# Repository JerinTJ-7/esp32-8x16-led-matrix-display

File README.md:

# ESP32 8×16 LED Matrix Display Board

## Overview

This project is a custom PCB-based LED matrix display designed using KiCad.

The system uses:
- ESP32 DevKit V1
- 74HC595 Shift Registers
- LED Matrix (8×16)
- Blynk IoT
- Wokwi Simulation

## Features

- Text display
- Scrolling messages
- Wi-Fi connectivity
- Mobile control using Blynk
- Custom KiCad PCB

## Tools Used

- KiCad 9
- Arduino IDE
- Wokwi Simulator
- Blynk IoT

## Images

## Files

- KiCad Design Files
- Gerbers
- BOM
- Arduino Firmware
- Project Report

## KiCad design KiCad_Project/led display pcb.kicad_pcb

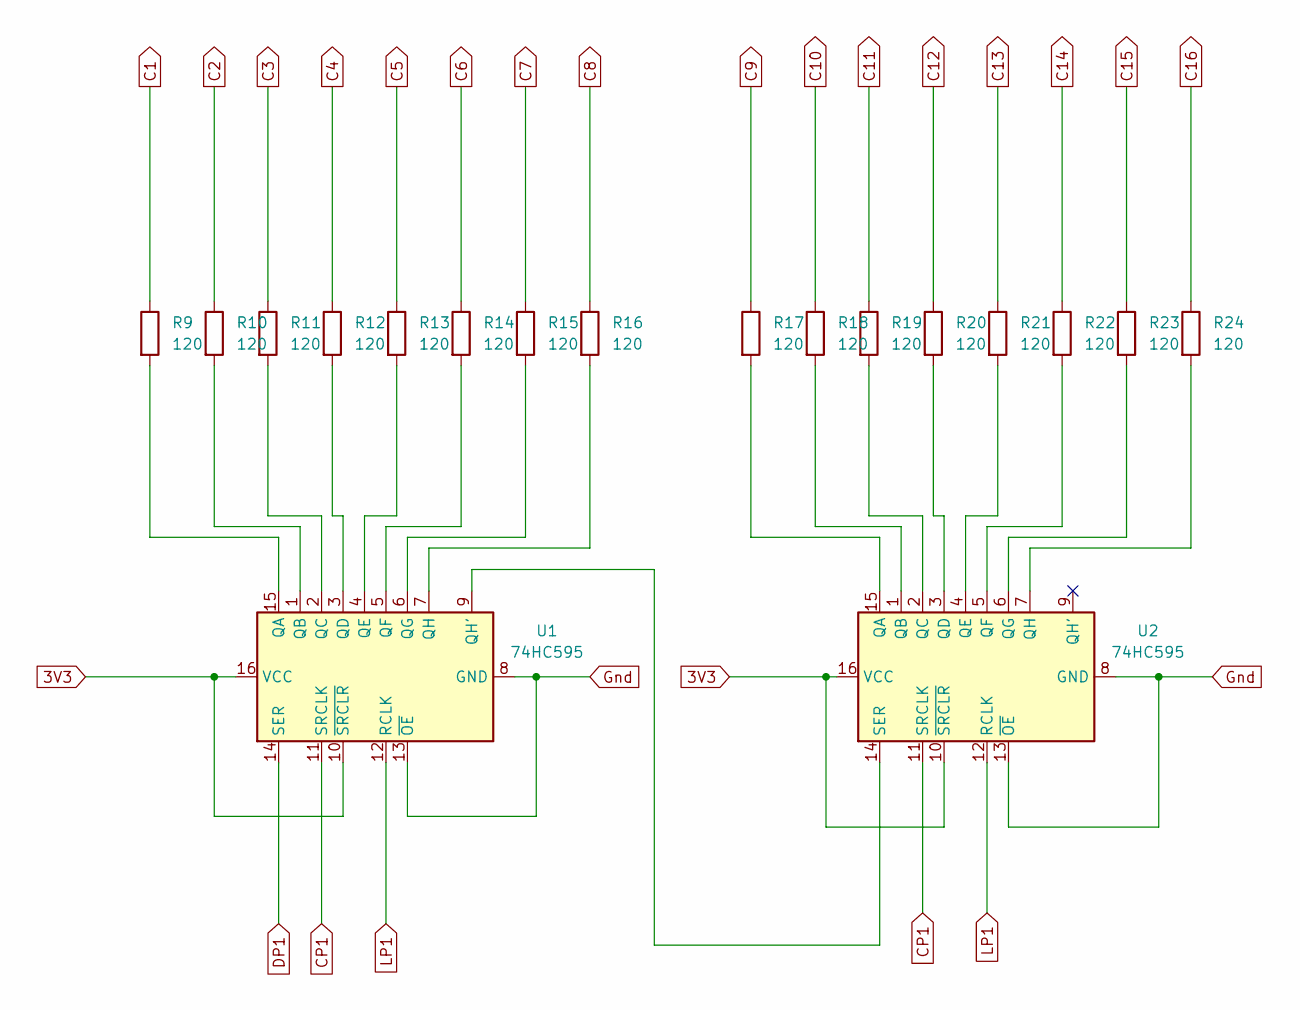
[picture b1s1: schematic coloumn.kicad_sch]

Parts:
R9, R10, R11, R12, R13, R14, R15, R16, R17, R18, R19, R20, R21, R22, R23, R24: 120; R_Axial_DIN0204_L3.6mm_D1.6mm_P5.08mm_Horizontal
U1, U2: 74HC595; DIP-16_W7.62mm

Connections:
3V3: U1.10 (~SRCLR), U1.16 (VCC), U2.10 (~SRCLR), U2.16 (VCC); also elsewhere on the board
C1: R9.1; also elsewhere on the board
C2: R10.1; also elsewhere on the board
C3: R11.1; also elsewhere on the board
C4: R12.1; also elsewhere on the board
C5: R13.1; also elsewhere on the board
C6: R14.1; also elsewhere on the board
C7: R15.1; also elsewhere on the board
C8: R16.1; also elsewhere on the board
C9: R17.1; also elsewhere on the board
C10: R18.1; also elsewhere on the board
C11: R19.1; also elsewhere on the board
C12: R20.1; also elsewhere on the board
C13: R21.1; also elsewhere on the board
C14: R22.1; also elsewhere on the board
C15: R23.1; also elsewhere on the board
C16: R24.1; also elsewhere on the board
CP1: U1.11 (SRCLK), U2.11 (SRCLK); also elsewhere on the board
DP1: U1.14 (SER); also elsewhere on the board
Gnd: U1.8 (GND), U1.13 (~OE), U2.8 (GND), U2.13 (~OE); also elsewhere on the board
LP1: U1.12 (RCLK), U2.12 (RCLK); also elsewhere on the board
unnamed: R9.2, U1.15 (QA)
unnamed: R10.2, U1.1 (QB)
unnamed: R11.2, U1.2 (QC)
unnamed: R12.2, U1.3 (QD)
unnamed: R13.2, U1.4 (QE)
unnamed: R14.2, U1.5 (QF)
unnamed: R15.2, U1.6 (QG)
unnamed: U1.9 (QH'), U2.14 (SER)
unnamed: R16.2, U1.7 (QH)
unnamed: R17.2, U2.15 (QA)
unnamed: R18.2, U2.1 (QB)
unnamed: R19.2, U2.2 (QC)
unnamed: R20.2, U2.3 (QD)
unnamed: R21.2, U2.4 (QE)
unnamed: R22.2, U2.5 (QF)
unnamed: R23.2, U2.6 (QG)
unnamed: R24.2, U2.7 (QH)

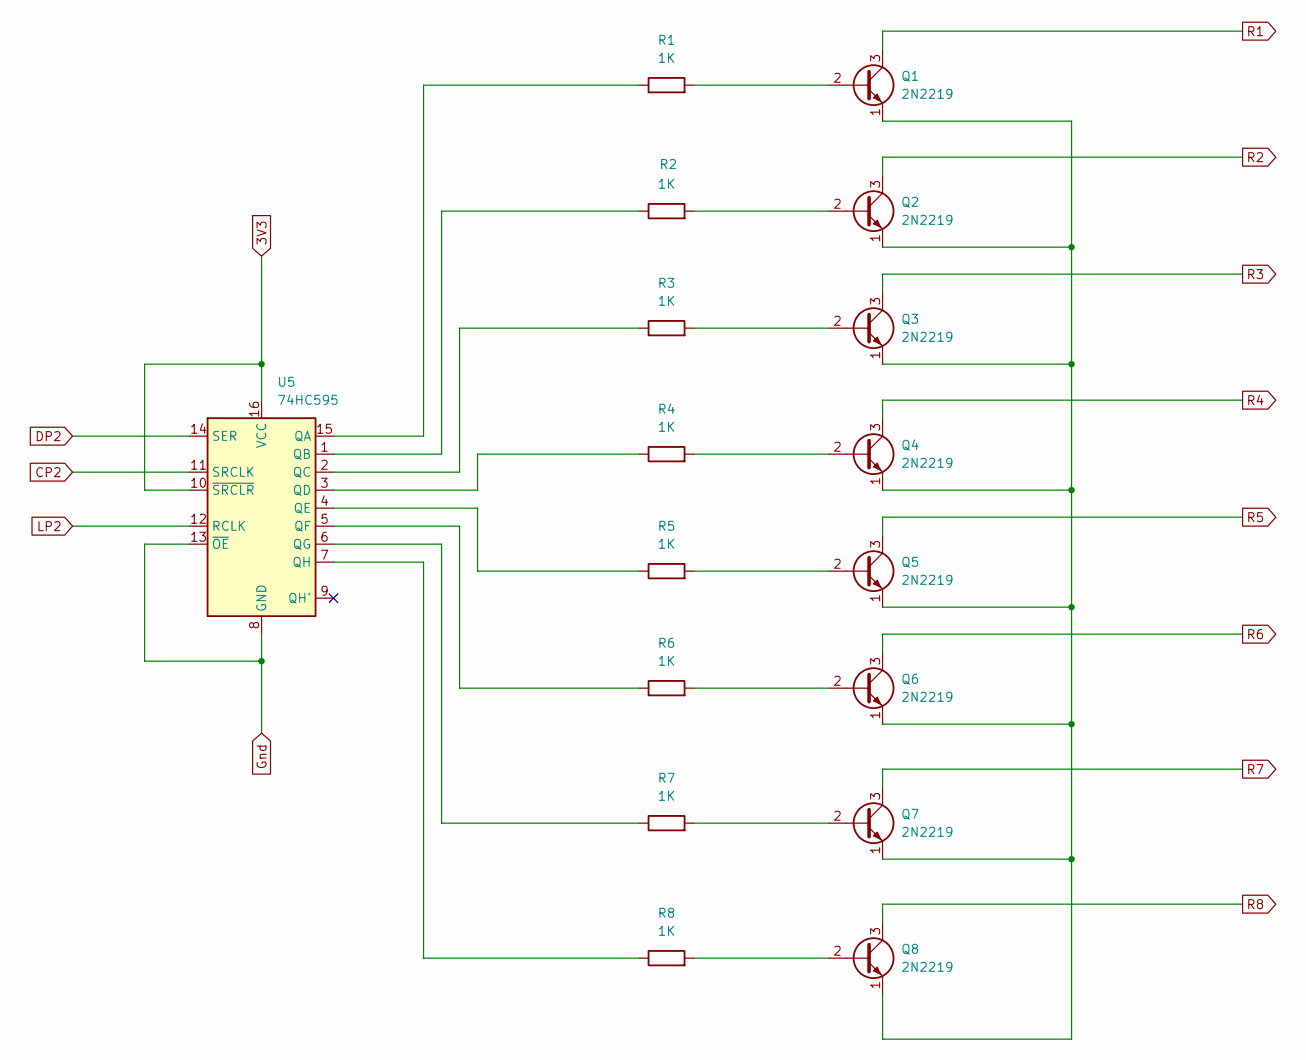
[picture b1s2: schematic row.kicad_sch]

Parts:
Q1, Q2, Q3, Q4, Q5, Q6, Q7, Q8: 2N2219; TO-39-3
R1, R2, R3, R4, R5, R6, R7, R8: 1K; R_Axial_DIN0204_L3.6mm_D1.6mm_P5.08mm_Horizontal
U5: 74HC595; DIP-16_W7.62mm

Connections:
3V3: U5.10 (~SRCLR), U5.16 (VCC); also elsewhere on the board
CP2: U5.11 (SRCLK); also elsewhere on the board
DP2: U5.14 (SER); also elsewhere on the board
Gnd: U5.8 (GND), U5.13 (~OE); also elsewhere on the board
LP2: U5.12 (RCLK); also elsewhere on the board
unnamed: Q1.2 (B), R1.2
unnamed: Q1.1 (E), Q2.1 (E), Q3.1 (E), Q4.1 (E), Q5.1 (E), Q6.1 (E), Q7.1 (E), Q8.1 (E)
unnamed: Q2.2 (B), R2.2
unnamed: Q3.2 (B), R3.2
unnamed: Q4.2 (B), R4.2
unnamed: Q5.2 (B), R5.2
unnamed: Q6.2 (B), R6.2
unnamed: Q7.2 (B), R7.2
unnamed: Q8.2 (B), R8.2
unnamed: R1.1, U5.15 (QA)
unnamed: R2.1, U5.1 (QB)
unnamed: R3.1, U5.2 (QC)
unnamed: R4.1, U5.3 (QD)
unnamed: R5.1, U5.4 (QE)
unnamed: R6.1, U5.5 (QF)
unnamed: R7.1, U5.6 (QG)
unnamed: R8.1, U5.7 (QH)
R1: Q1.3 (C); also elsewhere on the board
R2: Q2.3 (C); also elsewhere on the board
R3: Q3.3 (C); also elsewhere on the board
R4: Q4.3 (C); also elsewhere on the board
R5: Q5.3 (C); also elsewhere on the board
R6: Q6.3 (C); also elsewhere on the board
R7: Q7.3 (C); also elsewhere on the board
R8: Q8.3 (C); also elsewhere on the board

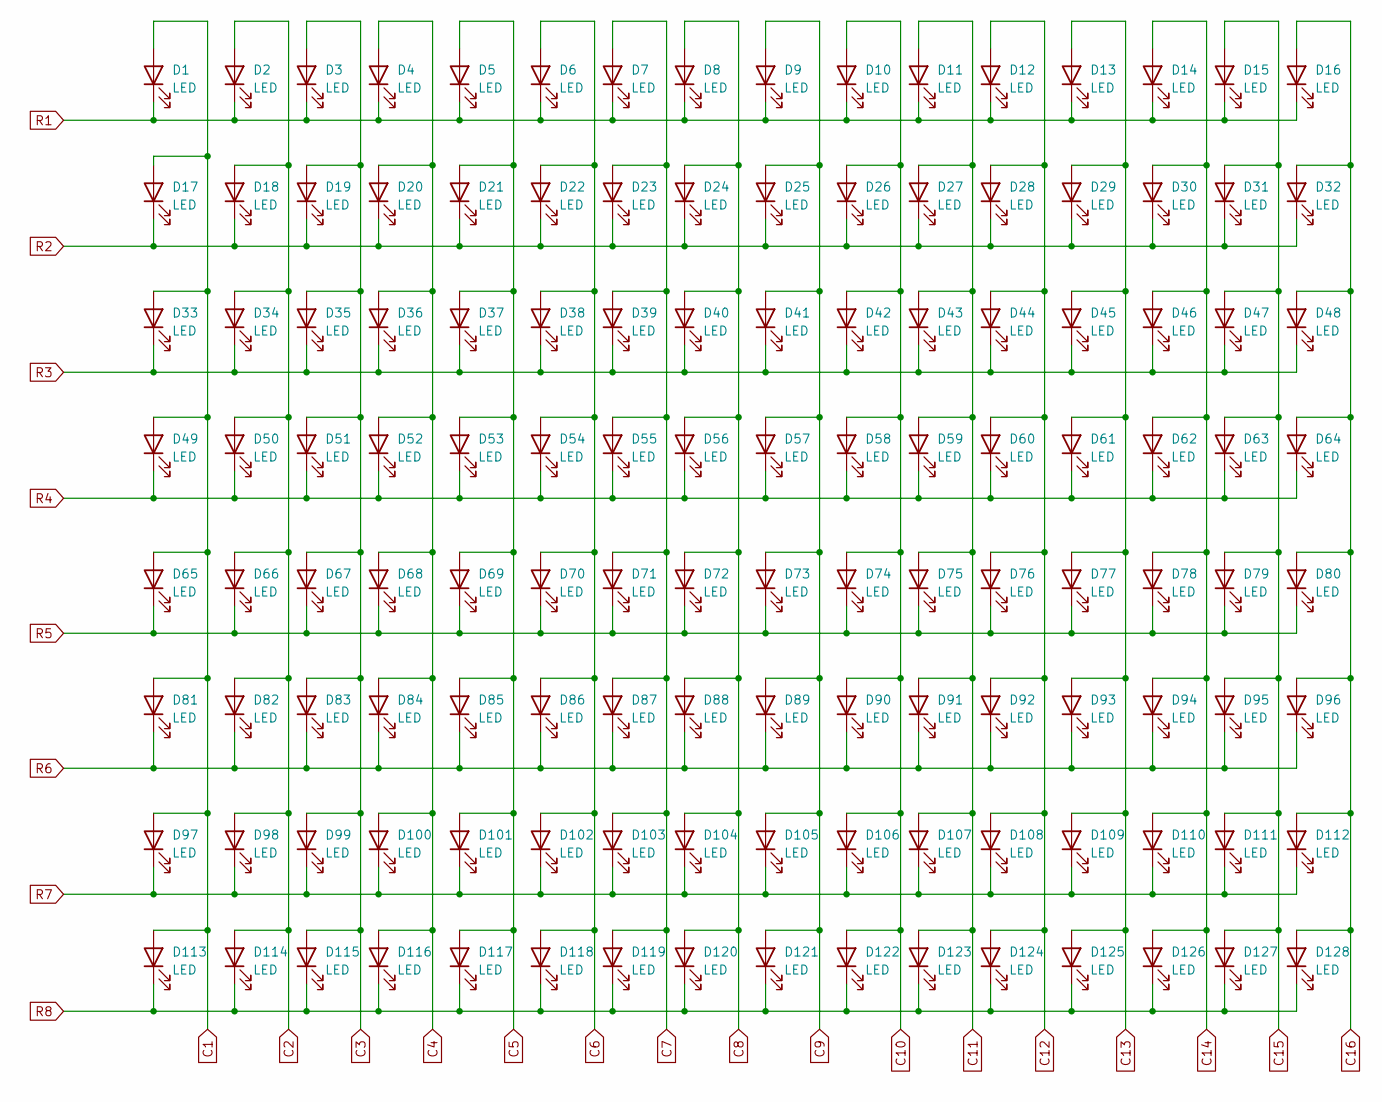
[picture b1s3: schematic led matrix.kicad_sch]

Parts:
D1, D2, D3, D4, D5, D6, D7, D8, D9, D10, D11, D12, D13, D14, D15, D16, D17, D18, D19, D20, D21, D22, D23, D24, D25, D26, D27, D28, D29, D30, D31, D32, D33, D34, D35, D36, D37, D38, D39, D40, D41, D42, D43, D44, D45, D46, D47, D48, D49, D50, D51, D52, D53, D54, D55, D56, D57, D58, D59, D60, D61, D62, D63, D64, D65, D66, D67, D68, D69, D70, D71, D72, D73, D74, D75, D76, D77, D78, D79, D80, D81, D82, D83, D84, D85, D86, D87, D88, D89, D90, D91, D92, D93, D94, D95, D96, D97, D98, D99, D100, D101, D102, D103, D104, D105, D106, D107, D108, D109, D110, D111, D112, D113, D114, D115, D116, D117, D118, D119, D120, D121, D122, D123, D124, D125, D126, D127, D128: LED; LED_D5.0mm

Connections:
C1: D1.2 (A), D17.2 (A), D33.2 (A), D49.2 (A), D65.2 (A), D81.2 (A), D97.2 (A), D113.2 (A); also elsewhere on the board
C2: D2.2 (A), D18.2 (A), D34.2 (A), D50.2 (A), D66.2 (A), D82.2 (A), D98.2 (A), D114.2 (A); also elsewhere on the board
C3: D3.2 (A), D19.2 (A), D35.2 (A), D51.2 (A), D67.2 (A), D83.2 (A), D99.2 (A), D115.2 (A); also elsewhere on the board
C4: D4.2 (A), D20.2 (A), D36.2 (A), D52.2 (A), D68.2 (A), D84.2 (A), D100.2 (A), D116.2 (A); also elsewhere on the board
C5: D5.2 (A), D21.2 (A), D37.2 (A), D53.2 (A), D69.2 (A), D85.2 (A), D101.2 (A), D117.2 (A); also elsewhere on the board
C6: D6.2 (A), D22.2 (A), D38.2 (A), D54.2 (A), D70.2 (A), D86.2 (A), D102.2 (A), D118.2 (A); also elsewhere on the board
C7: D7.2 (A), D23.2 (A), D39.2 (A), D55.2 (A), D71.2 (A), D87.2 (A), D103.2 (A), D119.2 (A); also elsewhere on the board
C8: D8.2 (A), D24.2 (A), D40.2 (A), D56.2 (A), D72.2 (A), D88.2 (A), D104.2 (A), D120.2 (A); also elsewhere on the board
C9: D9.2 (A), D25.2 (A), D41.2 (A), D57.2 (A), D73.2 (A), D89.2 (A), D105.2 (A), D121.2 (A); also elsewhere on the board
C10: D10.2 (A), D26.2 (A), D42.2 (A), D58.2 (A), D74.2 (A), D90.2 (A), D106.2 (A), D122.2 (A); also elsewhere on the board
C11: D11.2 (A), D27.2 (A), D43.2 (A), D59.2 (A), D75.2 (A), D91.2 (A), D107.2 (A), D123.2 (A); also elsewhere on the board
C12: D12.2 (A), D28.2 (A), D44.2 (A), D60.2 (A), D76.2 (A), D92.2 (A), D108.2 (A), D124.2 (A); also elsewhere on the board
C13: D13.2 (A), D29.2 (A), D45.2 (A), D61.2 (A), D77.2 (A), D93.2 (A), D109.2 (A), D125.2 (A); also elsewhere on the board
C14: D14.2 (A), D30.2 (A), D46.2 (A), D62.2 (A), D78.2 (A), D94.2 (A), D110.2 (A), D126.2 (A); also elsewhere on the board
C15: D15.2 (A), D31.2 (A), D47.2 (A), D63.2 (A), D79.2 (A), D95.2 (A), D111.2 (A), D127.2 (A); also elsewhere on the board
C16: D16.2 (A), D32.2 (A), D48.2 (A), D64.2 (A), D80.2 (A), D96.2 (A), D112.2 (A), D128.2 (A); also elsewhere on the board
R1: D1.1 (K), D2.1 (K), D3.1 (K), D4.1 (K), D5.1 (K), D6.1 (K), D7.1 (K), D8.1 (K), D9.1 (K), D10.1 (K), D11.1 (K), D12.1 (K), D13.1 (K), D14.1 (K), D15.1 (K), D16.1 (K); also elsewhere on the board
R2: D17.1 (K), D18.1 (K), D19.1 (K), D20.1 (K), D21.1 (K), D22.1 (K), D23.1 (K), D24.1 (K), D25.1 (K), D26.1 (K), D27.1 (K), D28.1 (K), D29.1 (K), D30.1 (K), D31.1 (K), D32.1 (K); also elsewhere on the board
R3: D33.1 (K), D34.1 (K), D35.1 (K), D36.1 (K), D37.1 (K), D38.1 (K), D39.1 (K), D40.1 (K), D41.1 (K), D42.1 (K), D43.1 (K), D44.1 (K), D45.1 (K), D46.1 (K), D47.1 (K), D48.1 (K); also elsewhere on the board
R4: D49.1 (K), D50.1 (K), D51.1 (K), D52.1 (K), D53.1 (K), D54.1 (K), D55.1 (K), D56.1 (K), D57.1 (K), D58.1 (K), D59.1 (K), D60.1 (K), D61.1 (K), D62.1 (K), D63.1 (K), D64.1 (K); also elsewhere on the board
R5: D65.1 (K), D66.1 (K), D67.1 (K), D68.1 (K), D69.1 (K), D70.1 (K), D71.1 (K), D72.1 (K), D73.1 (K), D74.1 (K), D75.1 (K), D76.1 (K), D77.1 (K), D78.1 (K), D79.1 (K), D80.1 (K); also elsewhere on the board
R6: D81.1 (K), D82.1 (K), D83.1 (K), D84.1 (K), D85.1 (K), D86.1 (K), D87.1 (K), D88.1 (K), D89.1 (K), D90.1 (K), D91.1 (K), D92.1 (K), D93.1 (K), D94.1 (K), D95.1 (K), D96.1 (K); also elsewhere on the board
R7: D97.1 (K), D98.1 (K), D99.1 (K), D100.1 (K), D101.1 (K), D102.1 (K), D103.1 (K), D104.1 (K), D105.1 (K), D106.1 (K), D107.1 (K), D108.1 (K), D109.1 (K), D110.1 (K), D111.1 (K), D112.1 (K); also elsewhere on the board
R8: D113.1 (K), D114.1 (K), D115.1 (K), D116.1 (K), D117.1 (K), D118.1 (K), D119.1 (K), D120.1 (K), D121.1 (K), D122.1 (K), D123.1 (K), D124.1 (K), D125.1 (K), D126.1 (K), D127.1 (K), D128.1 (K); also elsewhere on the board

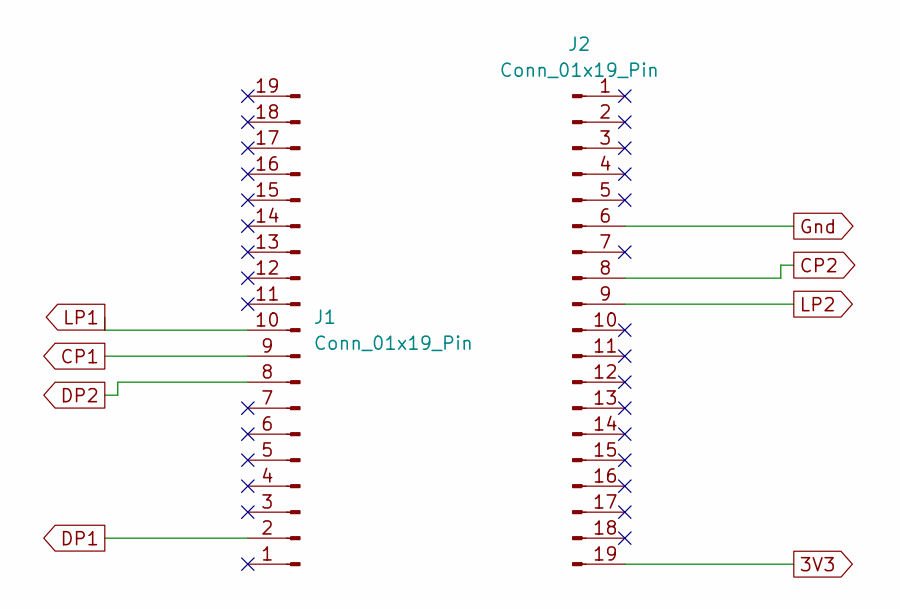
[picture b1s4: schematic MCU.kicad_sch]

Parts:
J1, J2: Conn_01x19_Pin; PinSocket_1x19_P2.54mm_Vertical

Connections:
3V3: J2.19; also elsewhere on the board
CP1: J1.9; also elsewhere on the board
CP2: J2.8; also elsewhere on the board
DP1: J1.2; also elsewhere on the board
DP2: J1.8; also elsewhere on the board
Gnd: J2.6; also elsewhere on the board
LP1: J1.10; also elsewhere on the board
LP2: J2.9; also elsewhere on the board

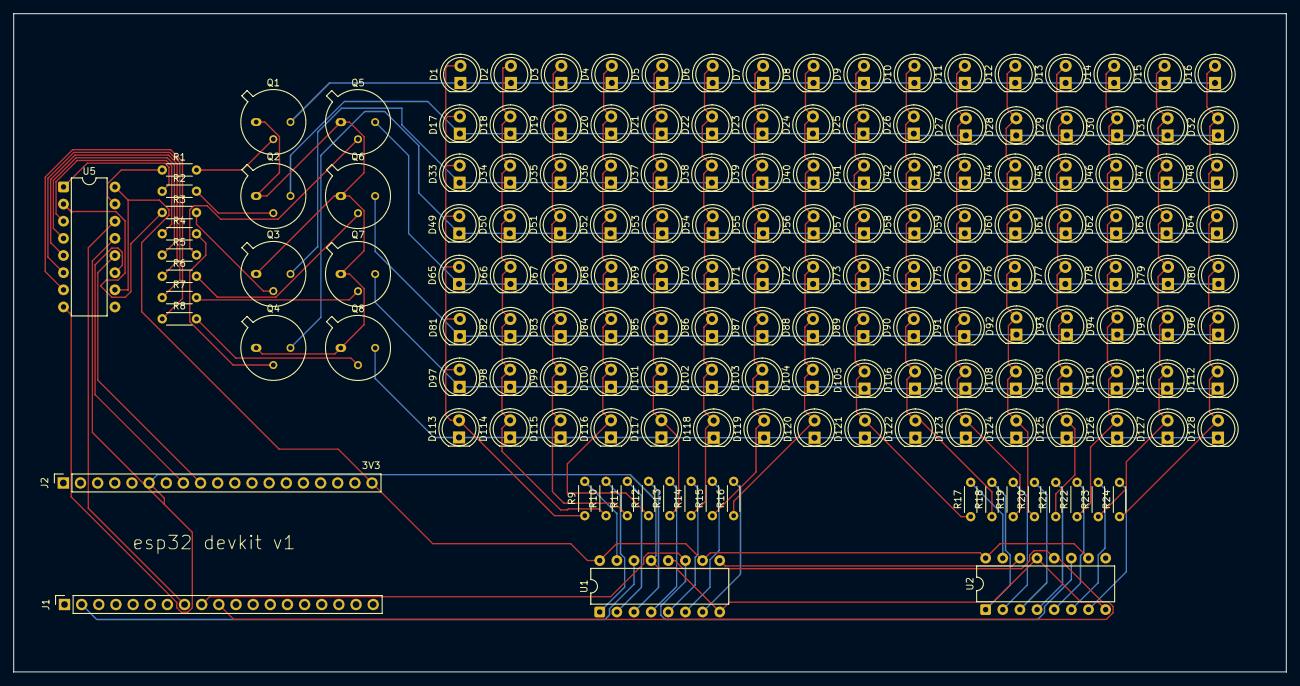
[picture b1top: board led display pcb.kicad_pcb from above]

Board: 2 copper layers, 188.5 x 97.5 mm, 165 parts (0 on the bottom side), 66 nets.
